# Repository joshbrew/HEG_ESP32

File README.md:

# HEG ESP32 - Open Source. Home of HEGduino!
Hemoencephalography meets highly affordable IoT! Now with WiFi and bluetooth! Incoming schematics, apps, and how-to's. [New Delobotomizer repo here](https://github.com/moothyknight/HEG_ESP32_Delobotomizer) for drivers for the new hardware.

Find the new, vastly easier to assembly HEGduino_V0 (3 parts, <10 dollars): https://github.com/joshbrew/hegduino_v0

Important HEGduino stuff you can find here:
- [HEG Training Quick Start Guide](https://github.com/moothyknight/HEG_ESP32/blob/master/Guides/HEG%20Training%20Quick%20Start%20Guide.pdf)
- [Progressive webapp (WIP) for Desktop or Android. Use with Chrome for now](https://hegalomania.netlify.app)
- [HEGduino Assembly](https://github.com/moothyknight/HEG_ESP32/blob/master/Guides/HEGduino%20Assembly%20Guide.pdf)
- [(For self-assembly only) Setting up Arduino to flash the ESP32 with our biofeedback software](https://github.com/moothyknight/HEG_ESP32/blob/master/Device_README.txt)
- [Updating the firmware via the web interface](https://github.com/moothyknight/HEG_ESP32/blob/master/Guides/How%20To%20Update.pdf)
- [Lolin32 Firmware and Updates](https://github.com/moothyknight/HEG_ESP32/tree/master/Device%20Drivers/HEG_WIFI_BLE_Lolin32)
- [Huzzah32 Feather Firmware and Updates](https://github.com/moothyknight/HEG_ESP32/tree/master/Device%20Drivers/HEG_WIFI_BLE_Feather)

## What is it?
Hemoencephalography is a single sensor FNIRS device meant to give a basic indication of cerebral blood flow changes in the brain.
Users then combine this indicator - the ratio of red to infrared light returned to the photodiode from the LEDs on your scalp or forehead - with simple visualization tools to help them increase or decrease metabolic/blood flow activity in the brain. 
This works like an odd form of physical therapy and is implicated as a powerful tool when combined in any brain health related therapies.

## Software

### Arduino Setup
See the [Device_Readme.txt](https://github.com/moothyknight/HEG_ESP32/blob/master/Device_README.txt)  for flashing instructions as well as available USB/WiFi/BLE commands and the changelog, including which dependencies are required for the Arduino IDE. We packaged the more minor dependencies in the Device_Drivers folder so you don't have to chase all of them down, just get Arduino and the ESP32 addon (github version) working.

Use the HEG_WIFI_BLE sketch in the arduino IDE on your respective ESP32. Pin definitions in HEG.h for the SDA/SCL and LEDs need to be adjusted according to your setup. 

These builds are tested on the Lolin32 and Huzzah32 Feather respectively but should work on any board after modifying the pinouts in HEG.h

### All Open Source Games, Tools, & APIs. See [the new PWA!](https://hegalomania.netlify.app)

On the firmware you will find a Async Web Server with a cross-platform supported javascript app, enabling plug-and-play and global networking features. We are creating an open source combined therapy and research toolset, using the perks of an online-enabled device and all of the diverse tools available for web front and backend. This is a living project so stay tuned!

You can demo it now at a new mobile or desktop-installable webapp at [hegalomania.netlify.app](https://hegalomania.netlify.app). 

The USB support on the PWA is chrome-only until it is out of development for default web support. Install on desktop by opening the setting dropdown in Chrome (the 3 vertical dots in the top right of the browser) and click "Install HEG Alpha." It should be kept up to date automatically and work offline. Make sure you have the Earth textures on the Sunrise mode cached to use them offline, simply load them once to do this.  

It's evolving fast. We will eventually be comparable to professional BCI software, free of charge. In the More folder, please find the DataCharting.html applet for analyzing and comparing your data with interactive charts.

## Data Charter (To be replaced) CSV analyzer for the web app (also found on our [Data page on our website](https://hegalpha.com))

## More Links
Our website: [HEG Alpha](https://hegalpha.com)

Find us on [CrowdSupply](https://crowdsupply.com/alaskit/hegduino)

and [OpenBCI](https://shop.openbci.com/collections/frontpage/products/hegduino-kit?variant=32052268531784)

Special thanks to the [Biocomp/Biofeedback Institute of LA](https://www.biocompresearch.org/), [Brain Trainer](https://brain-trainer.com/), and [AlasKit](https://alaskit.net)

See also (very deprecated):
[Arduino Nano V3 HEG](https://github.com/moothyknight/HEG_Arduino)

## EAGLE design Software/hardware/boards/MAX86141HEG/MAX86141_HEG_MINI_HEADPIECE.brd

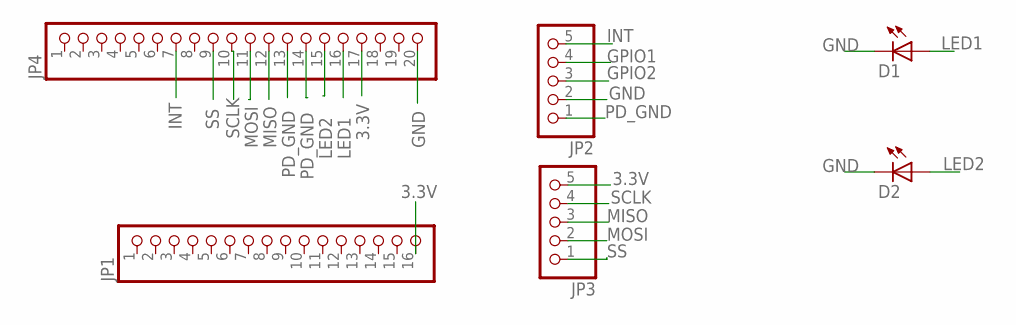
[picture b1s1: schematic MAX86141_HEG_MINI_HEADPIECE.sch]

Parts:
D1, D2: LED1206; LED-1206
JP1: PINHD-1X16; 1X16
JP2, JP3: PINHD-1X5; 1X05
JP4: PINHD-1X20; 1X20

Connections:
3.3V: JP1.16, JP3.5, JP4.17
GND: D1.C, D2.C, JP2.2, JP4.20
GPIO1: JP2.4
GPIO2: JP2.3
INT: JP2.5, JP4.7
LED1: D1.A, JP4.16
LED2: D2.A, JP4.15
MISO: JP3.3, JP4.12
MOSI: JP3.2, JP4.11
PD_GND: JP2.1, JP4.13, JP4.14
SCLK: JP3.4, JP4.10
SS: JP3.1, JP4.9

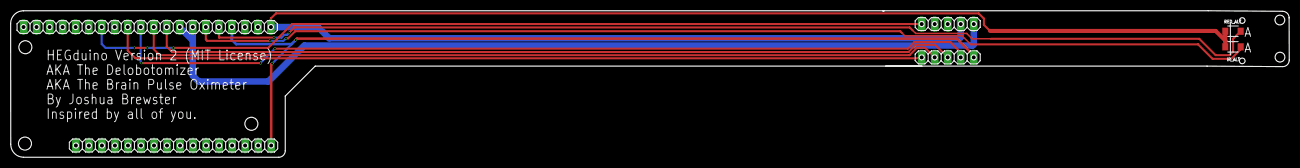
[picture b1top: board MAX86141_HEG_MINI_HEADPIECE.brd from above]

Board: 2 copper layers, 249.4 x 28.5 mm, 6 parts (0 on the bottom side), 10 nets.

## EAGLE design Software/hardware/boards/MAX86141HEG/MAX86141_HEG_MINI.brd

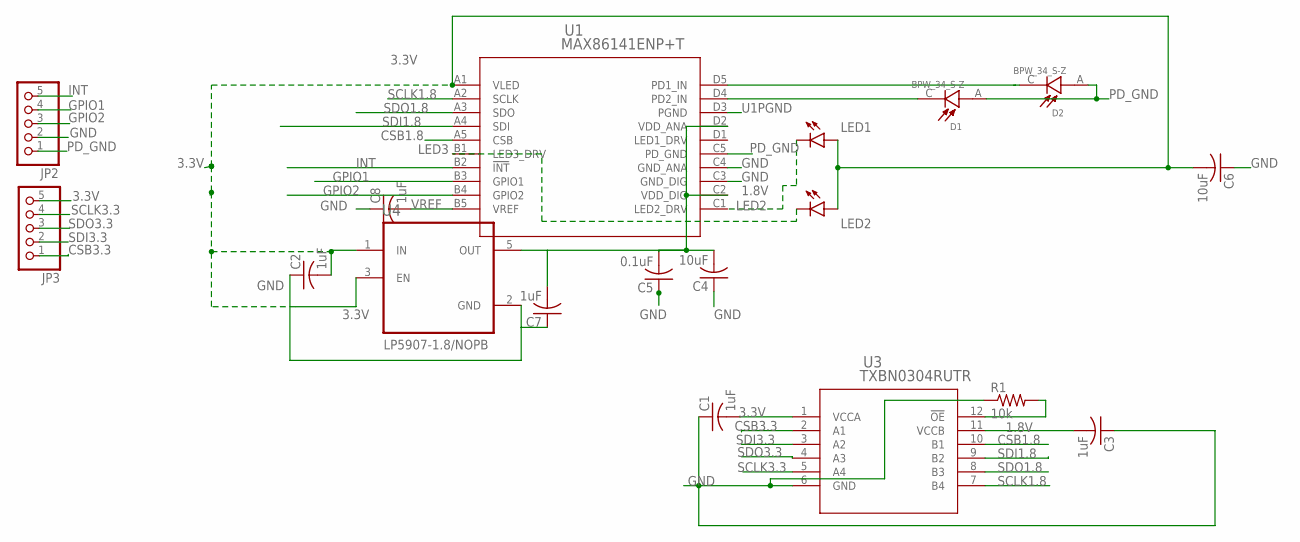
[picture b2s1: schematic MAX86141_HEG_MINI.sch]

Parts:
C1, C2, C3, C7, C8: 1uF; C0402
C4, C6: 10uF; C0402
C5: 0.1uF; C0402
D1, D2: BPW_34_S-Z; DIO_BPW_34_S-Z
JP2, JP3: PINHD-1X5; 1X05
LED1, LED2: LEDCHIPLED_1206; CHIPLED_1206
R1: 10k; R0402
U1: MAX86141ENP+T; 21-100134A_20
U3: TXBN0304RUTR; RUT12
U4: LP5907MFX-3.3/NOPB; SOT95P280X145-5N

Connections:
1.8V: C3.2, C4.2, C5.2, C7.2, U1.C2 (VDD_DIG), U1.D2 (VDD_ANA), U3.11 (VCCB), U4.5 (OUT)
3.3V: C1.2, C2.2, C6.2, JP3.5, LED1.A, LED2.A, U1.A1 (VLED), U3.1 (VCCA), U4.1 (IN), U4.3 (EN)
CSB1.8: U1.A5 (CSB), U3.10 (B1)
CSB3.3: JP3.1, U3.2 (A1)
GND: C1.1, C2.1, C3.1, C4.1, C5.1, C6.1, C7.1, C8.1, JP2.2, R1.1, U1.C3 (GND_DIG), U1.C4 (GND_ANA), U3.6 (GND), U4.2 (GND)
GPIO1: JP2.4, U1.B3 (GPIO1)
GPIO2: JP2.3, U1.B4 (GPIO2)
INT: JP2.5, U1.B2 (!INT)
LED2: LED1.C, U1.C1 (LED2_DRV)
LED3: LED2.C, U1.B1 (LED3_DRV)
OE: R1.2, U3.12 (!OE)
PD1_IN: D2.C, U1.D5 (PD1_IN)
PD2_IN: D1.C, U1.D4 (PD2_IN)
PD_GND: D1.A, D2.A, JP2.1, U1.C5 (PD_GND)
SCLK1.8: U1.A2 (SCLK), U3.7 (B4)
SCLK3.3: JP3.4, U3.5 (A4)
SDI1.8: U1.A4 (SDI), U3.9 (B2)
SDI3.3: JP3.2, U3.3 (A2)
SDO1.8: U1.A3 (SDO), U3.8 (B3)
SDO3.3: JP3.3, U3.4 (A3)
U1PGND: U1.D3 (PGND)
VREF: C8.2, U1.B5 (VREF)

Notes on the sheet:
LP5907-1.8/NOPB

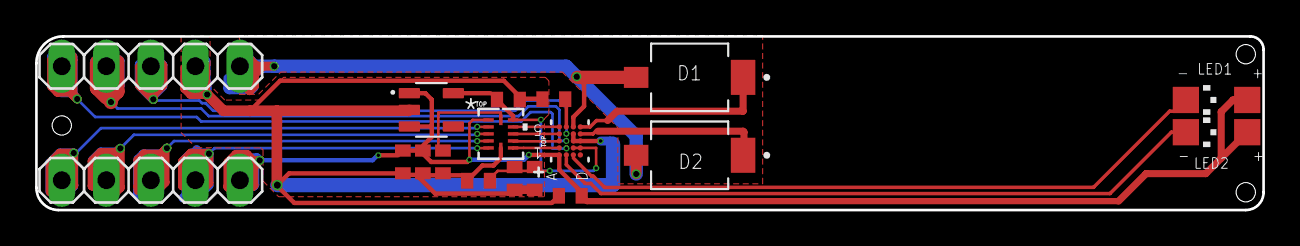
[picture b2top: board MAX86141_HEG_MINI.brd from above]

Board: 2 copper layers, 70.0 x 9.9 mm, 18 parts (0 on the bottom side), 21 nets.

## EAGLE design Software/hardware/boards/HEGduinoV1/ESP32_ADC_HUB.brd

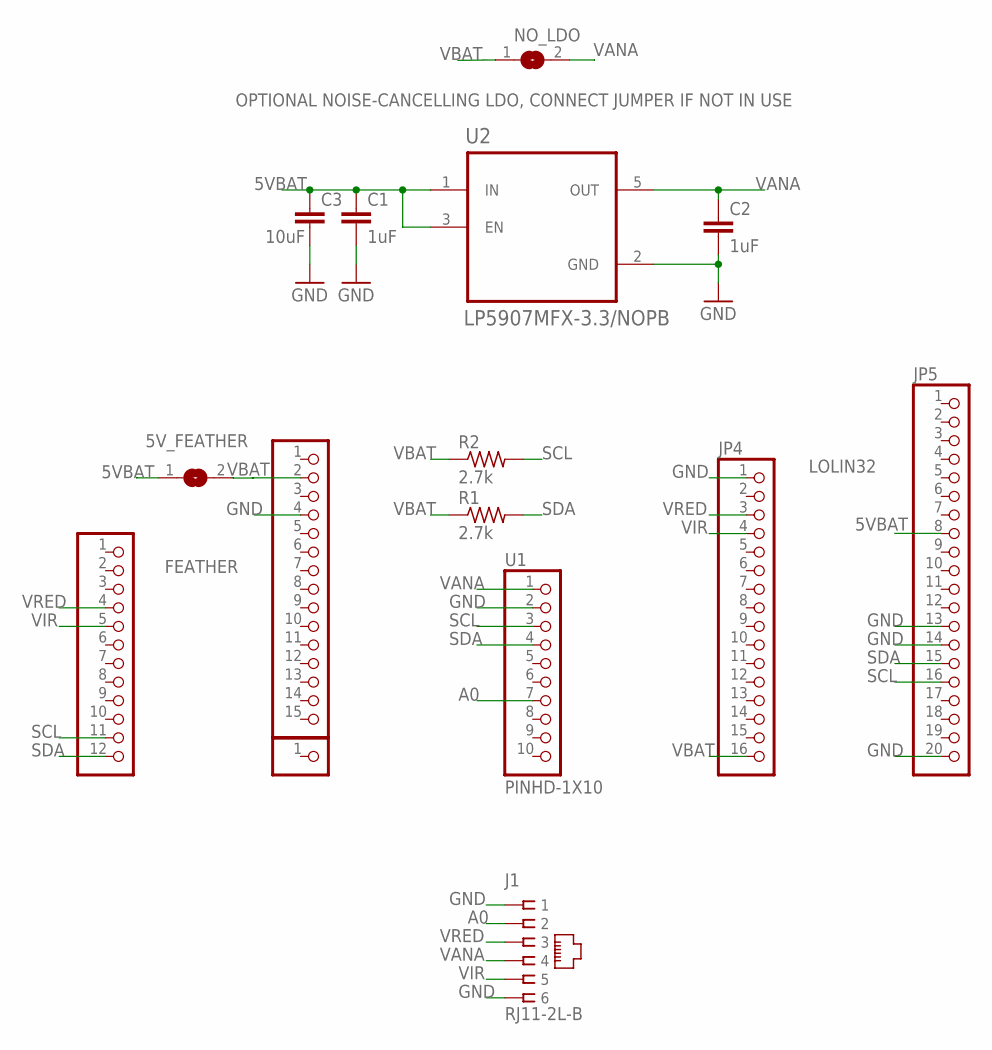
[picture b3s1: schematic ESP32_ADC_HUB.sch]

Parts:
5V_FEATHER: SJ
C1, C2: 1uF; C050-024X044
C3: 10uF; C050-024X044
J1: RJ11-2L-B; RJ11-NO_SHIELD
JP1: PINHD-1X12-CB; 1X12-CB
JP2: PINHD-1X15-CB; 1X15-CB
JP3: PINHD-1X1CB; 1X01-CLEANBIG
JP4: PINHD-1X16; 1X16
JP5: PINHD-1X20; 1X20
NO_LDO: SJ
R1, R2: 2.7k; 0204/7
U1: PINHD-1X10; 1X10-BIG
U2: LP5907MFX-3.3/NOPB; SOT95P280X145-5N

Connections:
5VBAT: 5V_FEATHER.1, C1.1, C3.1, JP5.8, U2.1 (IN), U2.3 (EN)
A0: J1.2, U1.7
GND: C1.2, C2.2, C3.2, J1.1, J1.6, JP2.4, JP4.1, JP5.13, JP5.14, JP5.20, U1.2, U2.2 (GND)
SCL: JP1.11, JP5.16, R2.2, U1.3
SDA: JP1.12, JP5.15, R1.2, U1.4
VANA: C2.1, J1.4, NO_LDO.2, U1.1, U2.5 (OUT)
VBAT: 5V_FEATHER.2, JP2.2, JP4.16, NO_LDO.1, R1.1, R2.1
VIR: J1.5, JP1.5, JP4.4
VRED: J1.3, JP1.4, JP4.3

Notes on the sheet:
OPTIONAL NOISE-CANCELLING LDO, CONNECT JUMPER IF NOT IN USE
FEATHER
LOLIN32

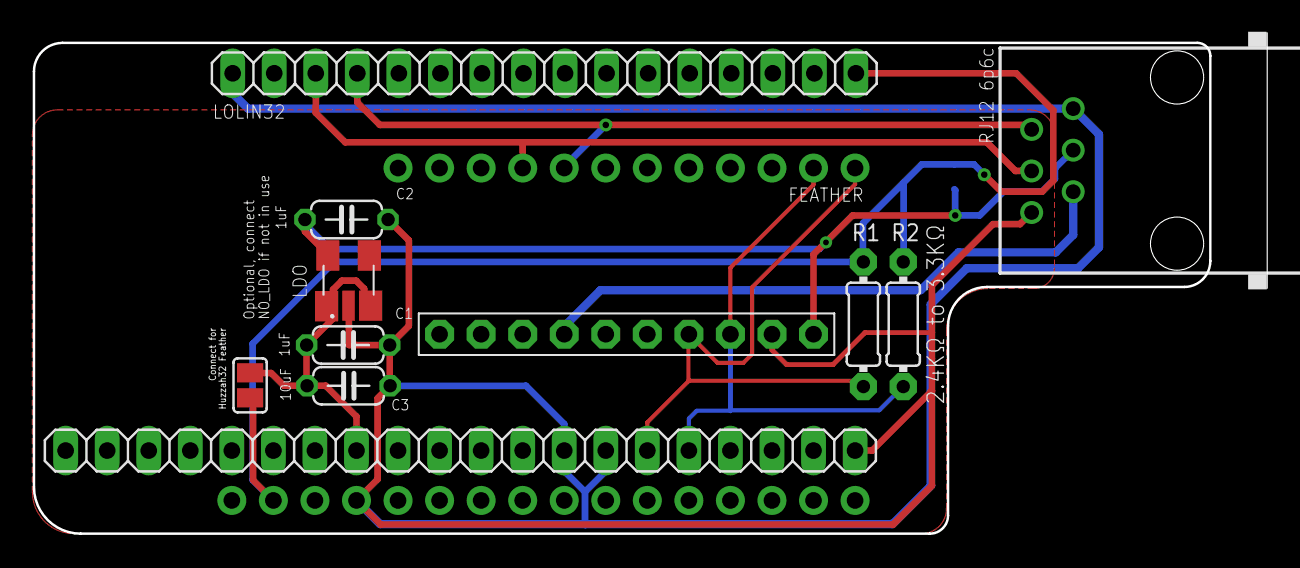
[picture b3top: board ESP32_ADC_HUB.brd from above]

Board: 2 copper layers, 75.3 x 30.5 mm, 15 parts (1 on the bottom side), 9 nets.

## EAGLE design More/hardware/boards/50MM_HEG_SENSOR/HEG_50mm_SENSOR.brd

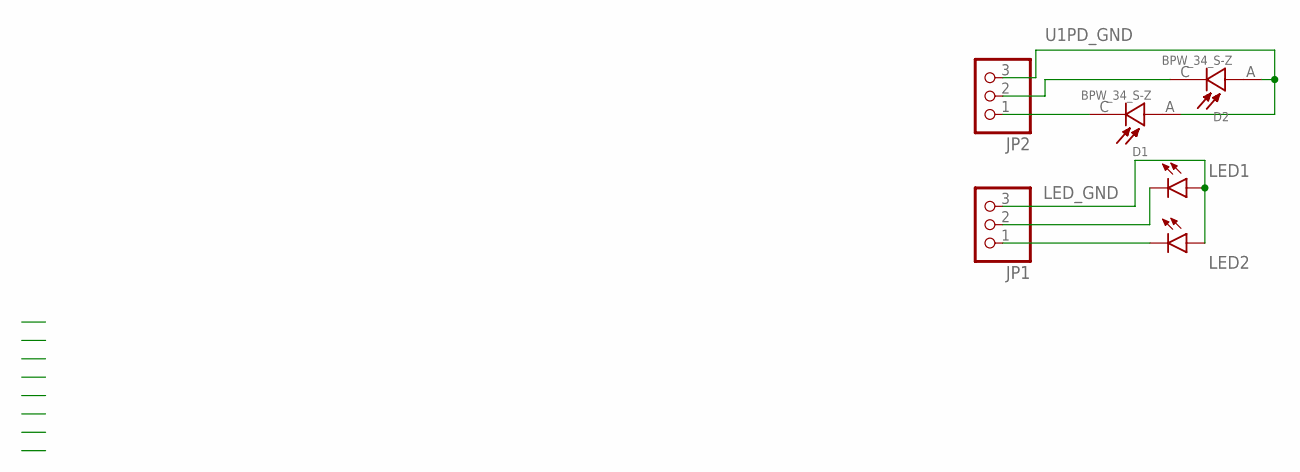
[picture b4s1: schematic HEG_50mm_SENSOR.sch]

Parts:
D1, D2: BPW_34_S-Z; DIO_BPW_34_S-Z
JP1, JP2: PINHD-1X3; 1X03
LED1, LED2: LEDCHIPLED_1206; CHIPLED_1206

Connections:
LED_GND: JP1.3, LED1.A, LED2.A
unnamed: JP1.1, LED2.C
unnamed: JP1.2, LED1.C
unnamed: D1.C, JP2.1
unnamed: D2.C, JP2.2
U1PD_GND: D1.A, D2.A, JP2.3

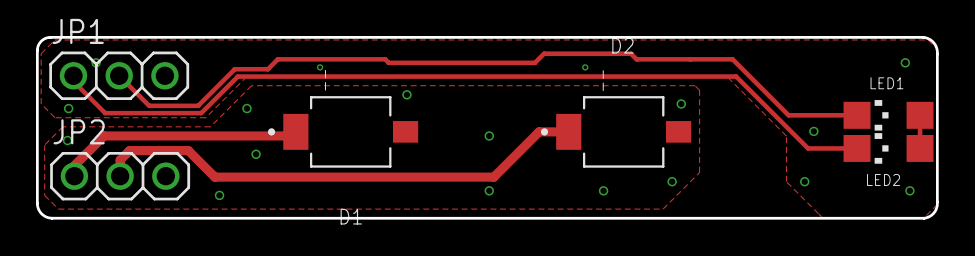
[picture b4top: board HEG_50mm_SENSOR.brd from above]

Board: 2 copper layers, 50.0 x 10.1 mm, 6 parts (0 on the bottom side), 6 nets.

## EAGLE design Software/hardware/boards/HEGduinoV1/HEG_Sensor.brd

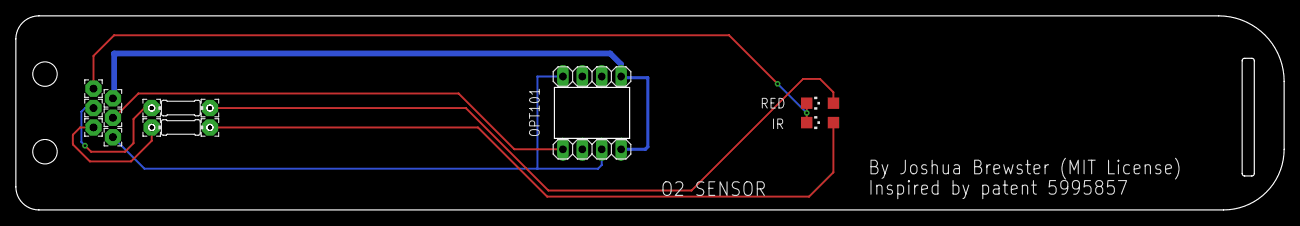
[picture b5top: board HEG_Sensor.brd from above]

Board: 2 copper layers, 166.0 x 25.4 mm, 17 parts (1 on the bottom side), 4 nets.

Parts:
E$1, E$2, E$3, E$4, E$5, E$6, E$7, E$8, E$9, E$10: 2,15/1,0
IR: DN1102W; CHIPLED_1206
J1: A-2004-1-4-LP-N-R; ASSMANN_A-2004-1-4-LP-N-R
JP2: 1X04
OPT101: 1X04
R1: 470; 0204/7
R2: 62; 0204/7
RED: BR1102W; CHIPLED_1206

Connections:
AIN0: J1.5, OPT101.4
VBAT: J1.3, JP2.1
VIR: J1.2, R1.2
VRED: J1.4, R2.2

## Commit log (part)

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2019-10-06 fix crash on mode switch, add static IP settings to /connect page
2019-10-07 working on video page
2019-10-07 sine wave webgl anim incoming (/graph)
    mining stackoverflow
2019-10-09 Added webGL based graphing to Canvas demo.
    Cool!!
2019-10-09 improve connect page
2019-10-09 minor quality of life changes
2019-10-09 fix radio buttons, add text overlay to graph
2019-10-10 small stuff
2019-10-10 save/replay
2019-10-10 save/load
2019-10-10 formatting
2019-10-11 create graphing class
2019-10-11 /hegvid updates
2019-10-12 migrating to class-based hierarchy for housekeeping
2019-10-12 fade & playbackrate toggles
2019-10-12 canvas demo UI now entirely class-based
2019-10-14 rename evs to webDemo, more improvements to Canvas Demo
    includes basic webGL api
2019-10-14 fix W command
2019-10-14 proper x scaling
2019-10-14 fix time value
2019-10-15 even classier, almost finished streamlining code.
2019-10-15 fix replay
2019-10-17 further improvements to webdemo (a couple bugs), dns options
2019-10-17 split web API
2019-10-17 more updates
2019-10-19 add audio mode (not best sound quality)
2019-10-19 event listener
2019-10-19 video tag unmuted
2019-10-19 fix period
2019-10-19 Audio quality fix
2019-10-19 Fix audio graph
2019-10-19 Fix audio
2019-10-19 made visualizer show volume changes
2019-10-19 fix audio switching
2019-10-22 add hill climb proof of concept
2019-10-22 add suggest IP option to test for a static IP if esp32.local does not work.
2019-10-22 minor change
2019-10-26 Forever open sourced!
2019-10-26 Forever Open Sourced! - ECAD files coming soon!
2019-10-29 Improve noise cancelling. Add help page (WIP)
2019-10-30 add other differential setting
2019-10-31 quick fix
2019-11-02 Removed a design (not fast enough adc)
2019-11-02 hotfix
2019-11-04 updates, more testing
2019-11-04 move event task to freeRTOS
2019-11-04 Add progress screenshot
2019-11-09 Disabled a broken feature
2019-11-09 Removed sav lay filter and changed programs to match (just need to recompile hegstudio)
2019-11-11 tweaks
2019-12-04 Sensor is FAST, but requires new libs. Updated help and added a compiled .bin for this version (upload via /update)
2019-12-09 Fixed sampling issues. Added support for StateofMind by Ben Hale
2019-12-09 fixed ADC and BLE
2019-12-10 slightly better signal, not ideal yet
2019-12-10 these timings are nonsensical
2019-12-11 fixed gpio, fixed sampling, need to address power supply
2019-12-11 Rolled back ADC library
2019-12-11 fixed, switched to SMA
2019-12-12 fixed web demo compat with rollback
2019-12-12 renamed update file with date
2019-12-12 added replay data that shows acceptable results
2019-12-12 added update how-to
2019-12-13 housekeeping, also made standalone html files for quicker editing
2019-12-13 replace update bin (may have been incorrect)
2019-12-14 added uninitialized API page for external apps to use. updated BP
2019-12-17 web UI update, see readme
2019-12-17 api page now easier to use for remote access. See info in code
2019-12-17 edit
2019-12-17 tweak
2019-12-19 added a design, updated HEGstudio image
2020-01-07 corrected some stuff
2020-01-23 big updates
2020-01-23 moved some stuff
2020-01-23 fixes
2020-01-26 guides
2020-01-27 edits to guides
2020-01-29 reuploaded bin
2020-01-30 updated assembly guide, help pages WIP
2020-01-30 added a pic
2020-01-30 moved readme
2020-02-01 minor updates/fixes
2020-02-07 Major web updates (plenty more coming)
2020-02-07 update bin
2020-02-07 more updates/fixes
2020-02-07 More UI updates
2020-02-07 UI Updates
2020-02-07 update photo
2020-02-08 moved HEGstudio to minimize file size
2020-02-12 graphing tweaks, annotating ability, etc.
2020-02-12 clarified
2020-02-13 exposed event source hosting option (for clients not hosted on-board but connected to same network)
2020-02-15 added a y offset slider and fixed fade mode
2020-02-15 update .bin files
2020-02-18 De-spaghetti'd some code
2020-02-18 edits
2020-02-18 demonstrating dynamic package adding
2020-02-18 merging some tweaks
2020-02-18 demonstrate ThreeJS rendering in context
2020-02-18 updoots
2020-02-18 three stuff
2020-02-18 generalized some stuff
2020-02-18 updatered and modificatered
2020-02-18 now the sphere spins
2020-02-18 some quick fixes and small tweaks
2020-02-19 updated with working ThreeJS exercise and more tweaks
2020-02-19 fixed bin files
2020-02-19 updated docs
2020-02-20 postprocessing
2020-02-20 recolor
2020-02-20 purty
2020-02-20 bloom
2020-02-20 updated threejs demo with postprocessing fx
2020-02-21 more UI improvements
2020-02-24 moved pdfs
2020-02-27 fixes and tweaks
2020-02-27 Moved files, added quick data analyzer html interface
2020-02-28 toying with style
2020-02-28 added some basic stats
2020-02-29 moved, updated data charting
2020-02-29 moved.
2020-02-29 Reformatted
2020-03-01 restored dark datachart, introduced error cat
2020-03-01 minor fixes
2020-03-02 added histograms and FFTs to DataCharter
2020-03-02 put fft in frequency domain correctly (I think?)
2020-03-02 cleaned up FFT spaghetti
2020-03-02 event handling
2020-03-02 dl csv from csv json
2020-03-03 fixed datacharter and annotating in webdemo, added note table to datacharter
2020-03-03 updated, fixed annotations, more recent sample data
2020-03-03 updated webapi SMA function, added basic fault testing for ratio (keeps within 25% error)
2020-03-03 fix to datacharter when posting several graphs at once
2020-03-04 slight fix to fault tolerance, updated version number to 0.1.6 and 0.0.6
2020-03-04 fixed compare button
2020-03-09 Added a folder of the additional dependencies for Arduino and ESP32
2020-03-09 reupload bin
2020-03-12 Reupload
2020-03-13 guides updated
2020-03-13 renamed
2020-03-14 updated BLE commands, added alternative ADC mode
2020-03-18 updated the Update guide
2020-03-18 added boards
2020-03-20 Fixed remote streaming capability, new feedback option (very basic), initial Chrome Extension support (with serial USB connectivity option incoming)
2020-03-20 fixed version numbers
2020-03-20 moved webdemo to standalone folder.
2020-03-20 added favicons and serial utils, still integrating it.
2020-03-21 working on serial usb mode for webapp via chrome extension
2020-03-21 Serial USB now supported, though needs some performance improvements
2020-03-22 improved graph performance (throttled requestAnimationFrame)
2020-03-22 fixed options
2020-03-22 moved stuff
2020-03-22 moved_stuff
2020-03-22 added Earth textures for ThreeJS module
2020-03-22 added specular, more physically correct rotation.
2020-03-22 quick fixes
2020-03-23 slight camera tweak
2020-03-23 updated diagrams in assembly guide and a few descriptions for clarity
2020-03-23 updated diagrams
2020-03-24 Reintroduced Bluetooth Serial support (plus LE!, 4 connectivity options now!)
2020-03-24 fix/moved stuff
2020-03-24 added clouds
2020-03-24 tweaked planet hue
2020-03-24 added some sunrise/sunset color
2020-03-24 rebuilt bins just in case of issues, also fixes the update progress bar
2020-03-24 now you should see the raw serial output for non-data (e.g. errors and IP info)
2020-03-25 added the moon, it orbits at an accurate scale, spin it a few days (or use threeApp.change in the console) and you get a solar eclipse
2020-03-25 fix for wifi mode not triggering
2020-03-26 fixed, added deep sleep mode (for battery saving)
2020-03-28 added tooltips to chrome extension
2020-03-28 re-fixed a thing
2020-03-29 updated firmware with tooltips
2020-03-29 added a new video mode (Time, this is equivalent to HEGstudio)
2020-03-29 pushed minor update
2020-03-31 reupload sketches
2020-03-31 fixed a boot sequence error
2020-04-04 changed 'u' command to toggle USB-only mode (no wireless coms), fixed autoscale issue
2020-04-16 quick fix for serial commands on chrome extension
2020-04-23 Added some sensor designs, moved some stuff
2020-05-01 updated output protocol, fixed BLE format, testing backend scripts (tflow, bcijs, and more)
2020-05-08 updated HEG schematic (1.1, testing it)
2020-05-08 hegduino 1.1 brd
2020-05-08 Uploaded canned MAX30112 design (untested). Somebody make this work!
2020-05-08 uploaded canned designs (be freeeeee!!!)
2020-05-09 upload schematic
2020-05-09 update schematic
2020-05-18 updated advanced design (need to test)
2020-05-26 0.0.9 update
2020-05-26 0.0.9; fixed hill scaling
2020-05-26 fixed circlejs soundfx conditional call
2020-06-01 0.0.10 update (features + fixes)
2020-06-02 tweaks and fixes, lower power consumption on LOLIN32, brd updates
2020-06-02 0.0.10 update pic
2020-06-02 deleted pics
2020-06-08 updated assembly guide
2020-07-16 updated webAPI, device stream format compatibility controllable via one liners and commands now. custom firmware now easier
2020-07-16 changelog
2020-07-19 moved js files, testing gpu.js
2020-07-20 wokring on gpu utils
2020-07-21 testing fft's, made graphNodes for ThreeJS for model trees
2020-07-22 more options in graphnodes
2020-07-24 hotfix to extension
2020-07-25 testing ffts
2020-07-26 fftjs result correction
2020-07-31 latest
2020-07-31 tested tflowjs (meh)
2020-08-24 re-ordered a couple links
2020-09-11 solve the covering issue on the intensity row
2020-09-11 minimize WiFi output power
2020-09-12 Minimize WiFi power in Feather
2020-09-14 Moved the hardware catalog to the main folder
2020-10-20 lolin32 firmware should update properly now
2020-10-21 new whitepaper
2020-10-24 Chrome BLE support plus convenience features (see changelog)
2020-10-25 more BLE experimenting
2020-10-25 cleanup
2020-10-25 testing faster output mode for BLE (20 pkt max)
2020-10-25 testing bluedroid fixes for lower MTU throughput (20 bytes/pkt)
2020-10-25 test fix
2020-10-25 ble fixes
2020-10-25 more fixes
2020-10-25 finally working the way it should
2020-10-25 pushing update with BLE and android fixes.
2020-10-26 timer fix
2020-10-26 fix timer for android, corrected feather build
2020-10-26 minor fixes for android code
2020-10-28 fixed word salad in abstract
2020-10-28 some other minor corrections
2020-10-29 boidyboids
2020-10-29 ever improving
2020-10-29 better boids separation
2020-10-30 how could I forget an image of data
2020-10-30 more info on the data
2020-10-31 more boids tweaks
2020-10-31 boids update on boards 0.1.12 update
2020-10-31 rename feather update file
2020-11-01 working multi channel DFT, yay!
2020-11-01 128 channel test for gpujs (its v good)
2020-11-02 gpujs testing
2020-11-05 11-5 updates
2020-11-06 reupload feather bin (just in case I compiled it wrong)
2020-11-06 commented out a debug thingy
2020-11-10 quick fix for lolin32 indicator
2020-11-13 minor updates to docs
2021-01-22 implement IIR filters (let me know if they help)
2021-01-23 fix build for feather
2021-02-08 rollback while fixing filters.
2021-03-03 formatting fix
2021-03-15 refresh lolin32 update file
2021-06-29 moved
2021-07-06 add images

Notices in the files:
Software/hardware/boards/HEGduinoV1/HEG_Sensor.brd:
By Joshua Brewster (MIT License)
Software/hardware/boards/MAX86141HEG/MAX86141_HEG_MINI.brd:
MAX86141 HEG MINI Prototype (MIT License)
Software/hardware/boards/MAX86141HEG/MAX86141_HEG_MINI_HEADPIECE.brd:
MAX86141 HEG MINI Mount Prototype (MIT License)
HEGduino Version 2 (MIT License)
parts and their libraries:
microbuilder_merge: This work is placed in the public domain, and may be freely used for commercial and non-commercial work with the following conditions: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
